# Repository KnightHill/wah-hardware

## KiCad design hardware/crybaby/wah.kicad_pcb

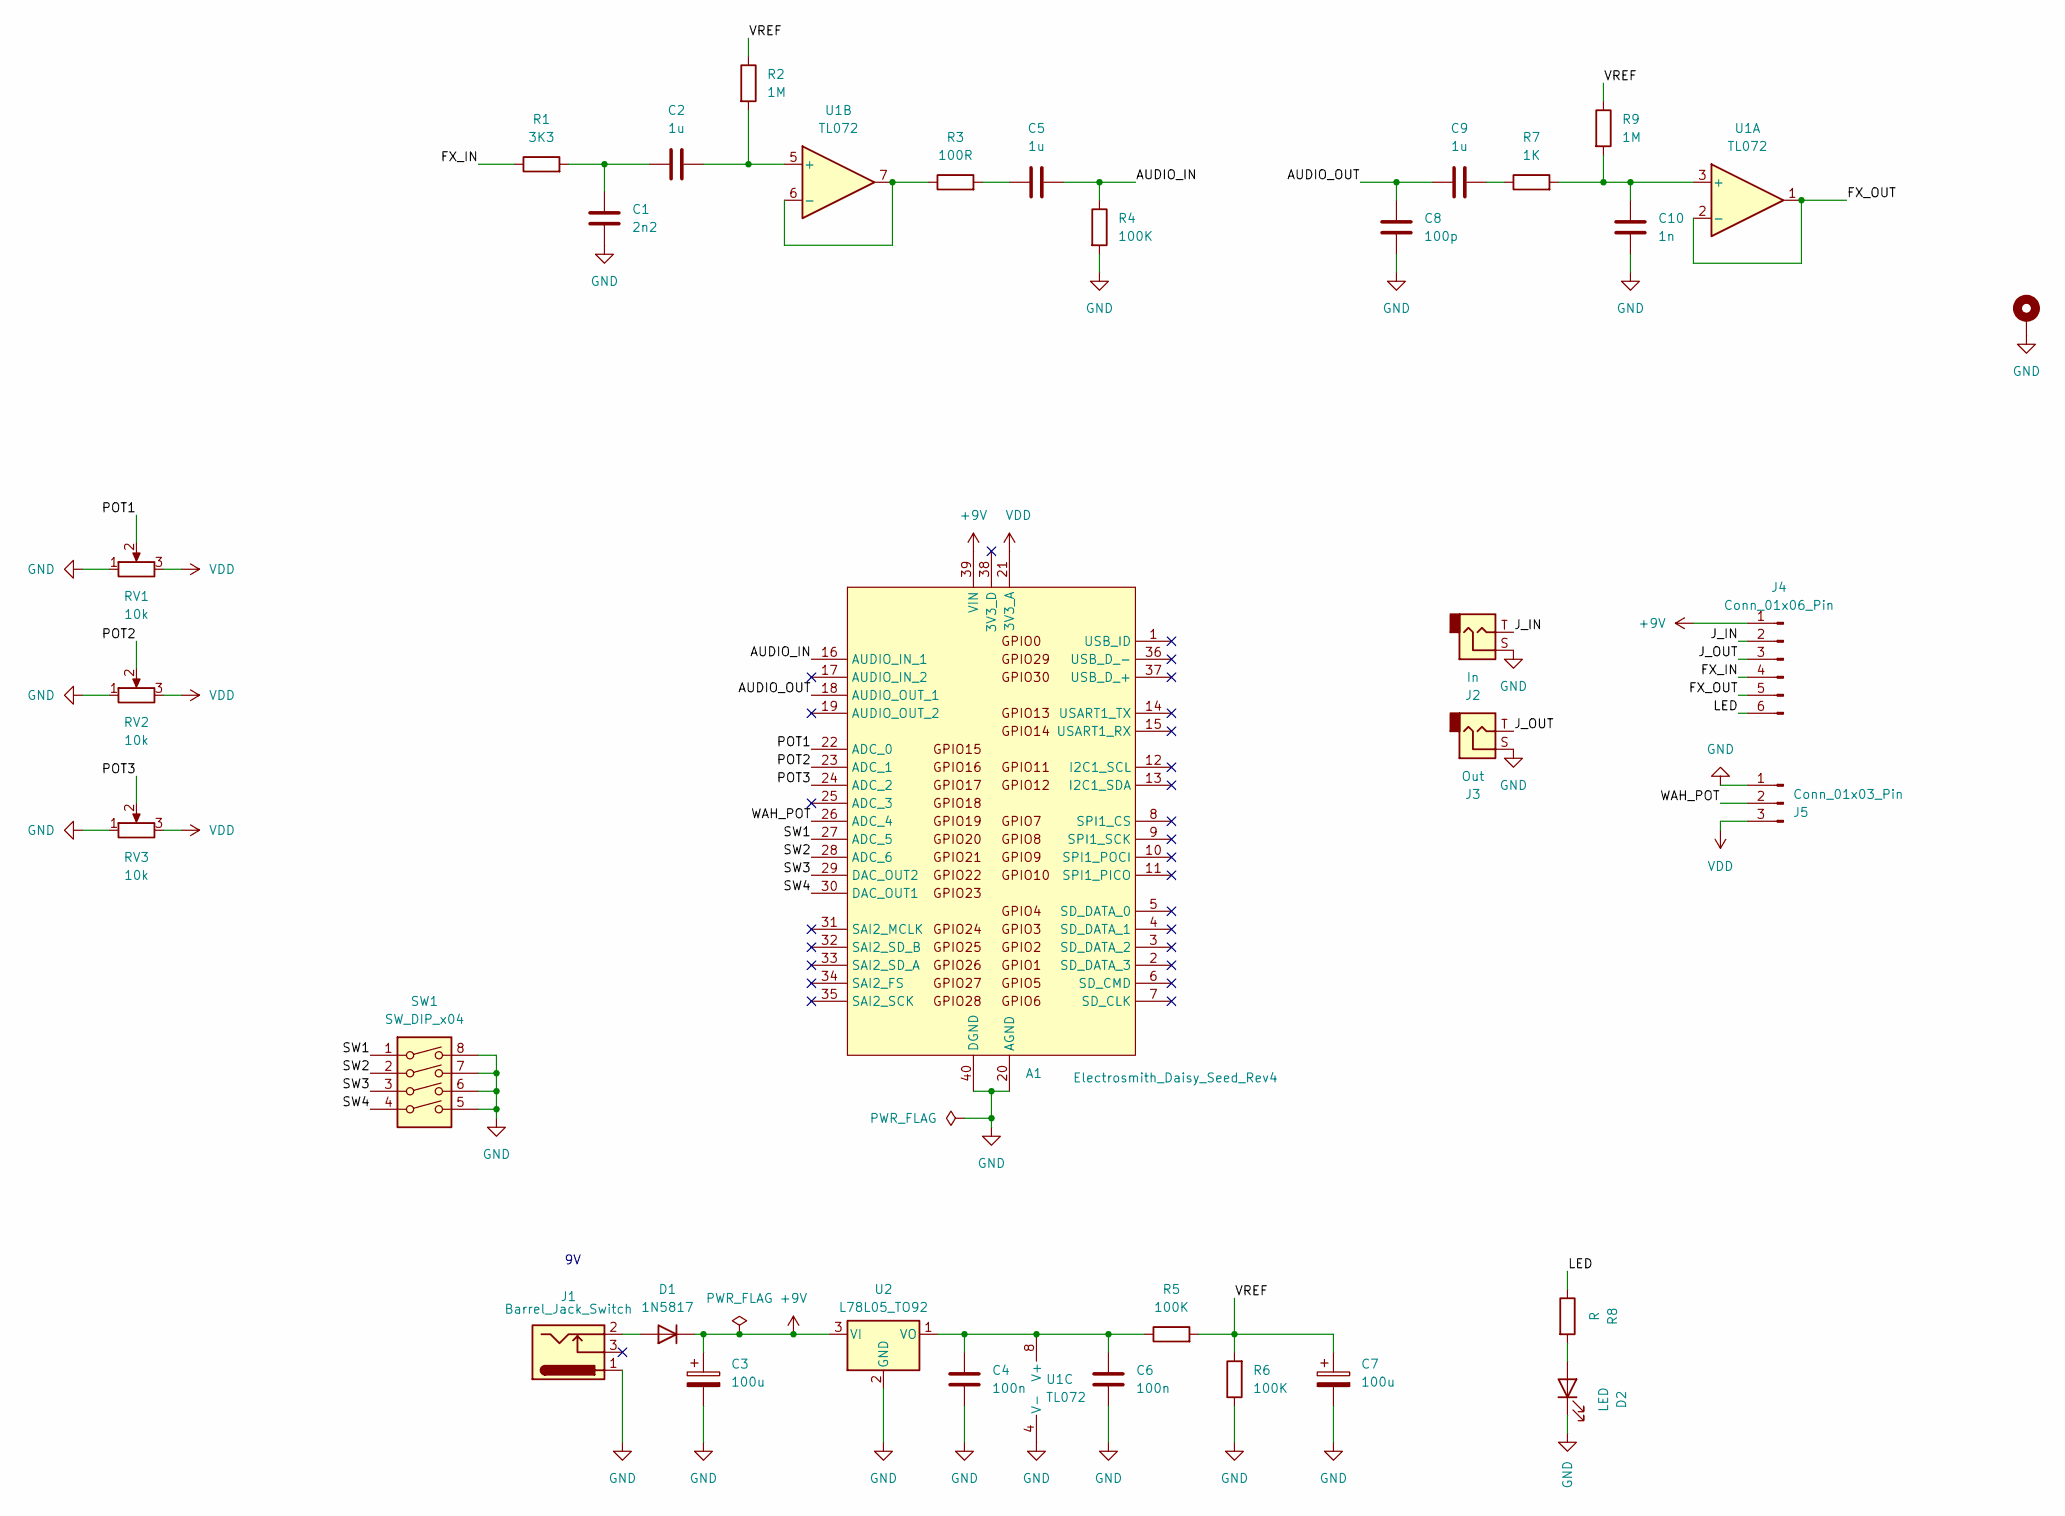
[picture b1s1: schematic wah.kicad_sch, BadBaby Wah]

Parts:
A1: Electrosmith_Daisy_Seed_Rev4; Electrosmith_Daisy_Seed
C1: 2n2; C_Rect_L7.0mm_W2.5mm_P5.00mm
C2, C5, C9: 1u; C_Rect_L7.0mm_W4.5mm_P5.00mm
C3, C7: 100u; CP_Radial_D5.0mm_P2.50mm
C4, C6: 100n; C_Rect_L7.0mm_W2.5mm_P5.00mm
C8: 100p; C_Rect_L7.0mm_W2.5mm_P5.00mm
C10: 1n; C_Rect_L7.0mm_W4.5mm_P5.00mm
D1: 1N5817; D_A-405_P7.62mm_Horizontal
D2: LED; LED_D5.0mm
H1: MountingHole_Pad; MountingHole_4.5mm_Pad
J1: Barrel_Jack_Switch; Generic_PowerJack
J2: In; Jack_6.35mm_Neutrik_NMJ4HCD2_Horizontal
J3: Out; Jack_6.35mm_Neutrik_NMJ4HCD2_Horizontal
J4: Conn_01x06_Pin; PinHeader_1x06_P2.54mm_Vertical
J5: Conn_01x03_Pin; PinHeader_1x03_P2.54mm_Vertical
R1: 3K3; R_Axial_DIN0207_L6.3mm_D2.5mm_P7.62mm_Horizontal
R2, R9: 1M; R_Axial_DIN0207_L6.3mm_D2.5mm_P7.62mm_Horizontal
R3: 100R; R_Axial_DIN0207_L6.3mm_D2.5mm_P7.62mm_Horizontal
R4, R5, R6: 100K; R_Axial_DIN0207_L6.3mm_D2.5mm_P7.62mm_Horizontal
R7: 1K; R_Axial_DIN0207_L6.3mm_D2.5mm_P7.62mm_Horizontal
R8: R; R_Axial_DIN0207_L6.3mm_D2.5mm_P7.62mm_Horizontal
RV1, RV2, RV3: 10k; 3362P
SW1: SW_DIP_x04; SW_DIP_SPSTx04_Slide_9.78x12.34mm_W7.62mm_P2.54mm
U1: TL072; DIP-8_W7.62mm
U2: L78L05_TO92; TO-92_Inline_Wide

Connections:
+9V: A1.39 (VIN), C3.1, D1.1 (K), J4.1, U2.3 (VI)
/AUDIO_IN: A1.16 (AUDIO_IN_1), C5.2, R4.1
/AUDIO_OUT: A1.18 (AUDIO_OUT_1), C8.1, C9.1
/FX_IN: J4.4, R1.1
/FX_OUT: J4.5, U1.1, U1.2 (-)
/J_IN: J2.T, J4.2
/J_OUT: J3.T, J4.3
/LED: J4.6, R8.1
/POT1: A1.22 (ADC_0), RV1.2
/POT2: A1.23 (ADC_1), RV2.2
/POT3: A1.24 (ADC_2), RV3.2
/SW1: A1.27 (ADC_5), SW1.1
/SW2: A1.28 (ADC_6), SW1.2
/SW3: A1.29 (DAC_OUT2), SW1.3
/SW4: A1.30 (DAC_OUT1), SW1.4
/VREF: C7.1, R2.1, R5.2, R6.2, R9.1
/WAH_POT: A1.26 (ADC_4), J5.2
GND: A1.20 (AGND), A1.40 (DGND), C1.2, C3.2, C4.2, C6.2, C7.2, C8.2, C10.2, D2.1 (K), H1.1, J1.1, J2.S, J3.S, J5.1, R4.2, R6.1, RV1.1, RV2.1, RV3.1, SW1.5, SW1.6, SW1.7, SW1.8, U1.4 (V-), U2.2 (GND)
unnamed: C1.1, C2.1, R1.2
unnamed: C5.1, R3.2
unnamed: C9.2, R7.1
unnamed: D1.2 (A), J1.2
unnamed: D2.2 (A), R8.2
unnamed: C10.1, R7.2, R9.2, U1.3 (+)
unnamed: C2.2, R2.2, U1.5 (+)
unnamed: R3.1, U1.6 (-), U1.7
unnamed: C4.1, C6.1, R5.1, U1.8 (V+), U2.1 (VO)
VDD: A1.21 (3V3_A), J5.3, RV1.3, RV2.3, RV3.3

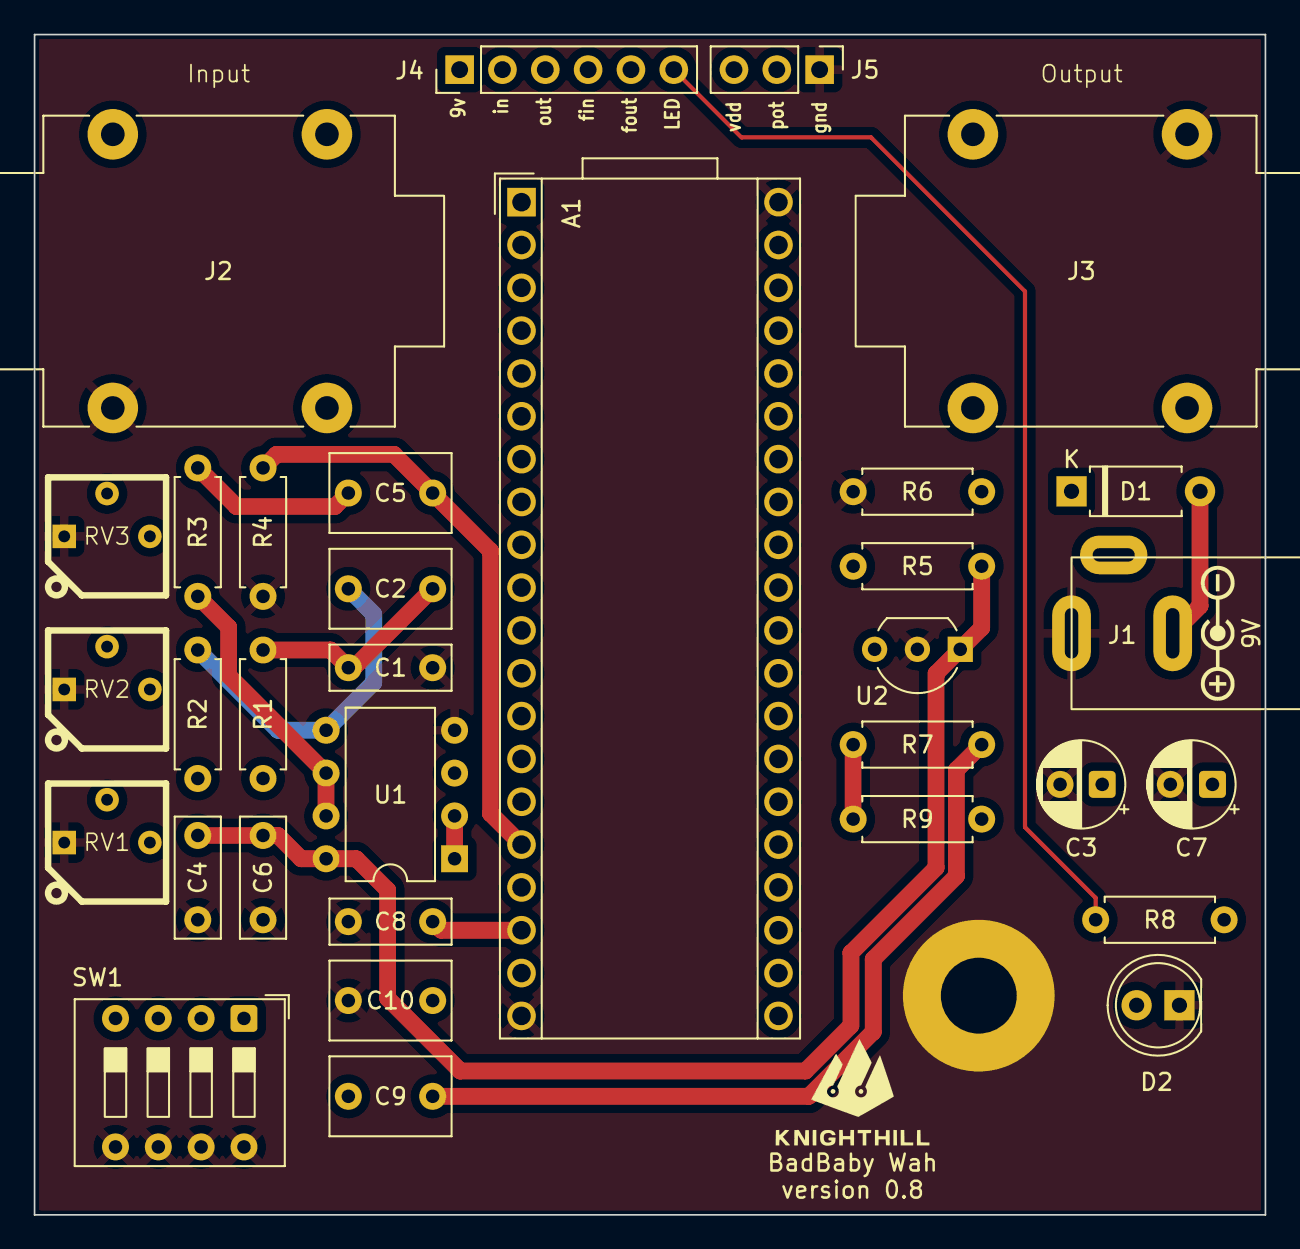
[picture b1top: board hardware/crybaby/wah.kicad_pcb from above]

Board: 4 copper layers, 73.0 x 70.0 mm, 34 parts (0 on the bottom side), 28 nets.

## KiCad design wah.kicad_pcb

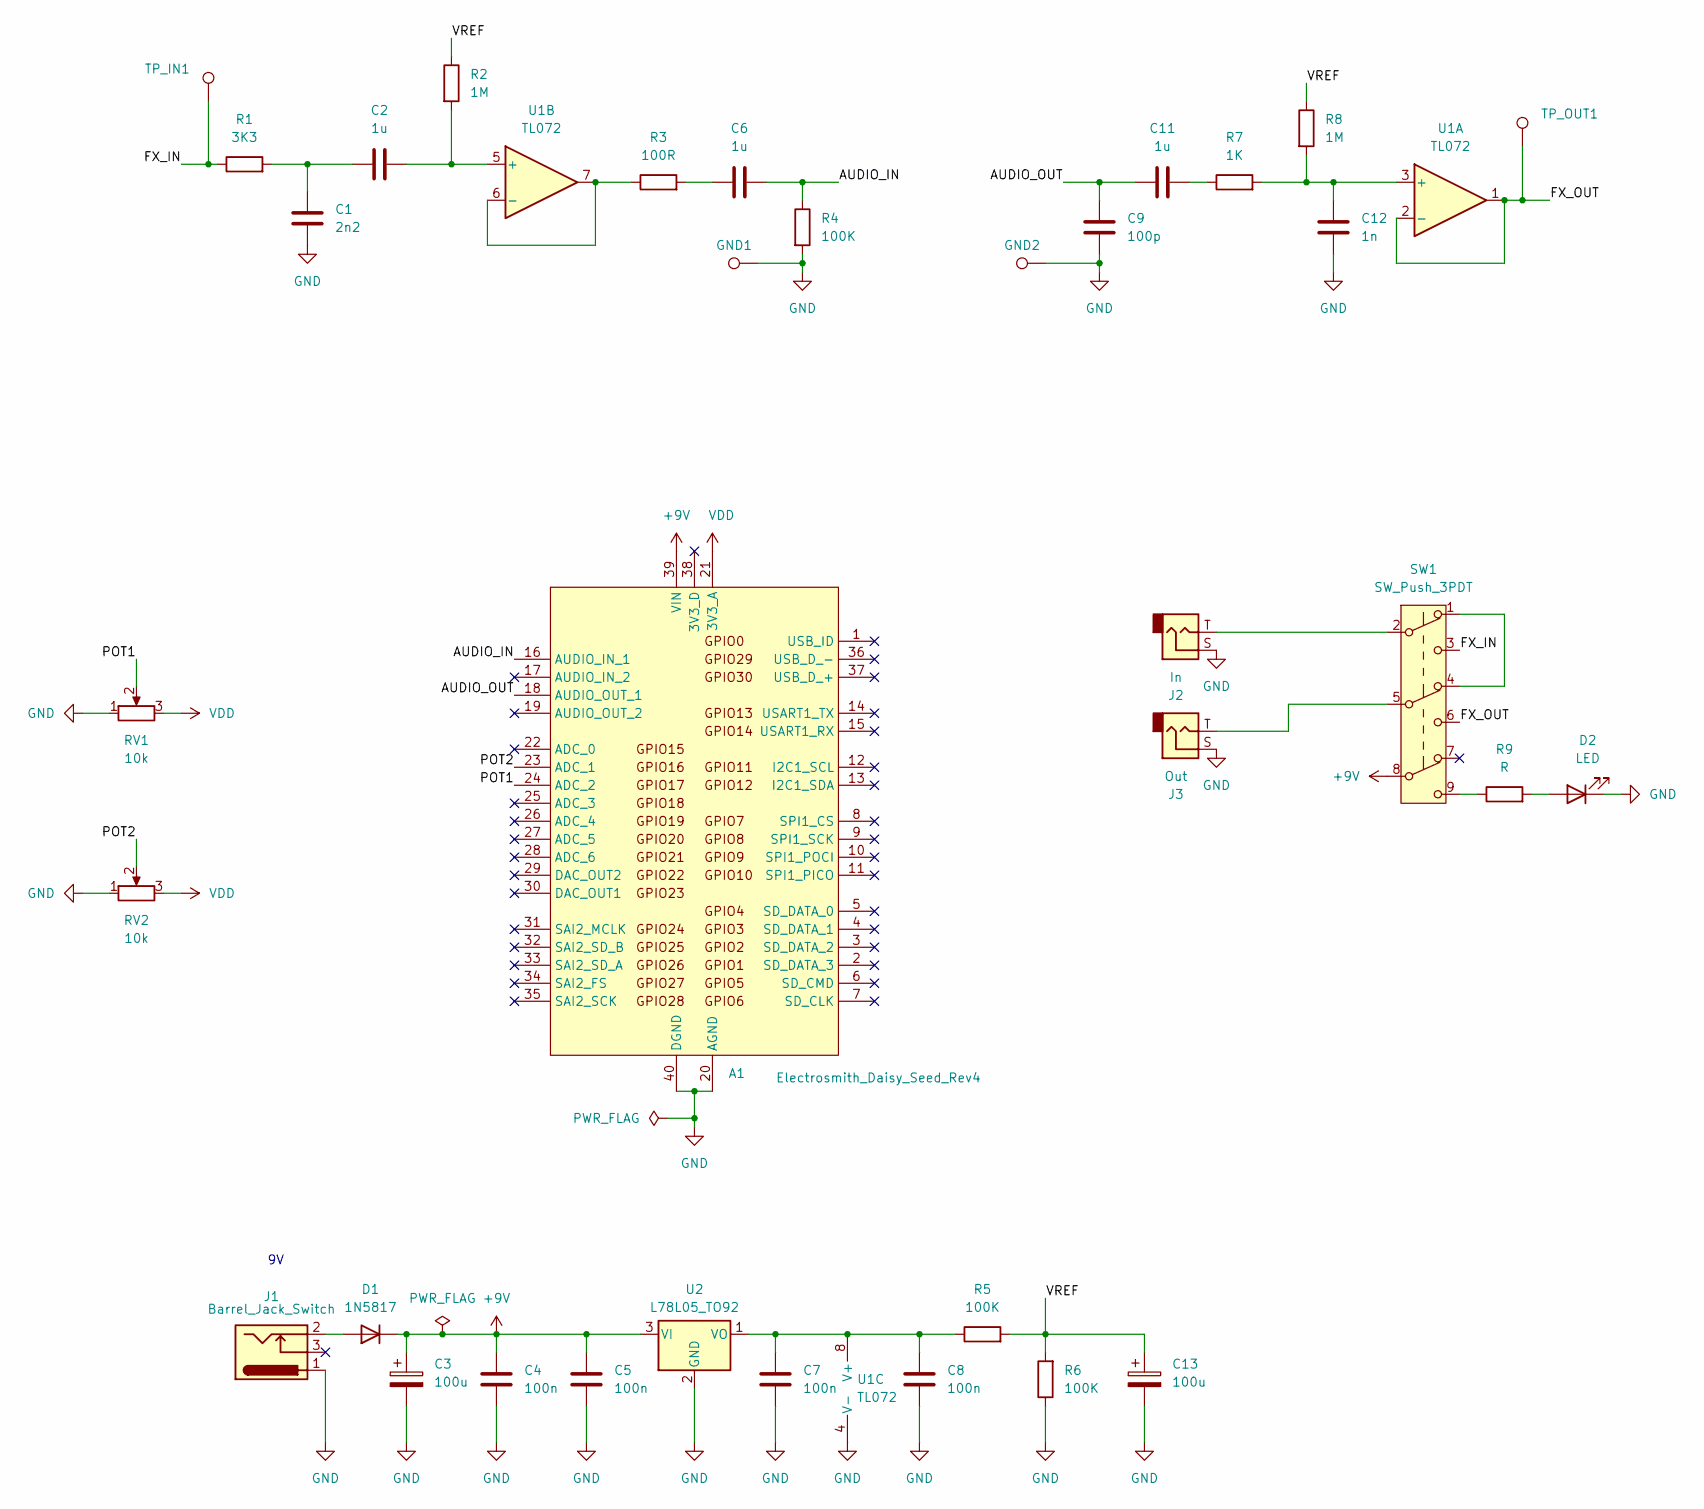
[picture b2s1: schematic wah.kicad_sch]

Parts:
A1: Electrosmith_Daisy_Seed_Rev4; Electrosmith_Daisy_Seed
C1: 2n2; C_Rect_L7.0mm_W2.5mm_P5.00mm
C2, C6, C11: 1u; C_Rect_L7.0mm_W2.5mm_P5.00mm
C3, C13: 100u; CP_Radial_D6.3mm_P2.50mm
C4, C5, C7, C8: 100n; C_Rect_L7.0mm_W2.5mm_P5.00mm
C9: 100p; C_Rect_L7.0mm_W2.5mm_P5.00mm
C12: 1n; C_Rect_L7.0mm_W2.5mm_P5.00mm
D1: 1N5817; D_A-405_P7.62mm_Horizontal
D2: LED; LED_D5.0mm
GND1, GND2: TestPoint_THTPad_1.5x1.5mm_Drill0.7mm
J1: Barrel_Jack_Switch; Generic_PowerJack
J2: In; Jack_6.35mm_Neutrik_NMJ4HCD2_Horizontal
J3: Out; Jack_6.35mm_Neutrik_NMJ4HCD2_Horizontal
R1: 3K3; R_Axial_DIN0207_L6.3mm_D2.5mm_P7.62mm_Horizontal
R2, R8: 1M; R_Axial_DIN0207_L6.3mm_D2.5mm_P7.62mm_Horizontal
R3: 100R; R_Axial_DIN0207_L6.3mm_D2.5mm_P7.62mm_Horizontal
R4, R5, R6: 100K; R_Axial_DIN0207_L6.3mm_D2.5mm_P7.62mm_Horizontal
R7: 1K; R_Axial_DIN0207_L6.3mm_D2.5mm_P7.62mm_Horizontal
R9: R; R_Axial_DIN0207_L6.3mm_D2.5mm_P7.62mm_Horizontal
RV1, RV2: 10k; Potentiometer_uxcel_9mm_Single_Vertical
SW1: SW_Push_3PDT; Switches_Stomp_Switch_3PDT
TP_IN1: TestPoint; TestPoint_THTPad_1.5x1.5mm_Drill0.7mm
TP_OUT1: TestPoint; TestPoint_THTPad_1.5x1.5mm_Drill0.7mm
U1: TL072; DIP-8_W7.62mm
U2: L78L05_TO92; TO-92_Inline_Wide

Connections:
+9V: A1.39 (VIN), C3.1, C4.1, C5.1, D1.1 (K), SW1.8 (B), U2.3 (VI)
/AUDIO_IN: A1.16 (AUDIO_IN_1), C6.2, R4.1
/AUDIO_OUT: A1.18 (AUDIO_OUT_1), C9.1, C11.1
/FX_IN: R1.1, SW1.3 (C), TP_IN1.1
/FX_OUT: SW1.6 (C), TP_OUT1.1, U1.1, U1.2 (-)
/POT1: A1.24 (ADC_2), RV1.2
/POT2: A1.23 (ADC_1), RV2.2
/VREF: C13.1, R2.1, R5.2, R6.2, R8.1
GND: A1.20 (AGND), A1.40 (DGND), C1.2, C3.2, C4.2, C5.2, C7.2, C8.2, C9.2, C12.2, C13.2, D2.1 (K), GND1.1, GND2.1, J1.1, J2.S, J3.S, R4.2, R6.1, RV1.1, RV2.1, U1.4 (V-), U2.2 (GND)
unnamed: C1.1, C2.1, R1.2
unnamed: C6.1, R3.2
unnamed: C11.2, R7.1
unnamed: D1.2 (A), J1.2
unnamed: D2.2 (A), R9.2
unnamed: J2.T, SW1.2 (B)
unnamed: J3.T, SW1.5 (B)
unnamed: R9.1, SW1.9 (C)
unnamed: SW1.1 (A), SW1.4 (A)
unnamed: C12.1, R7.2, R8.2, U1.3 (+)
unnamed: C2.2, R2.2, U1.5 (+)
unnamed: R3.1, U1.6 (-), U1.7
unnamed: C7.1, C8.1, R5.1, U1.8 (V+), U2.1 (VO)
VDD: A1.21 (3V3_A), RV1.3, RV2.3

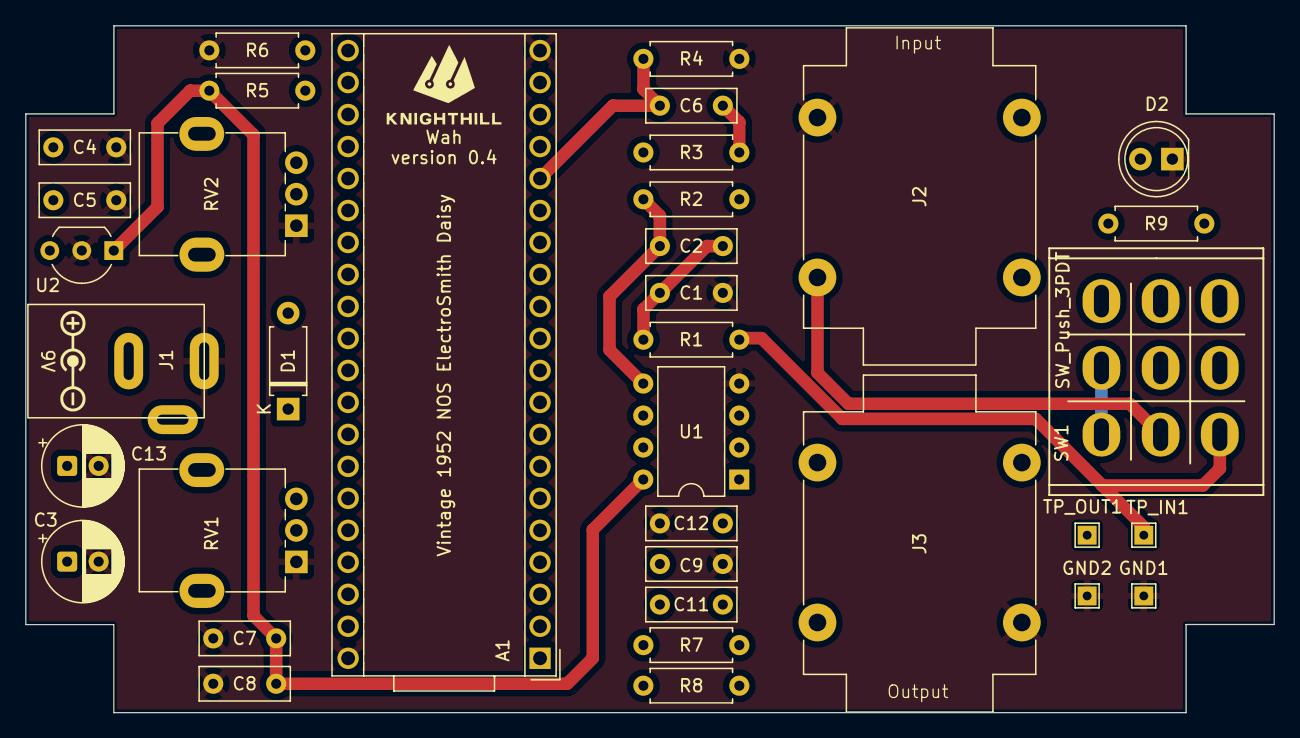
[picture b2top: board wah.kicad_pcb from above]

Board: 4 copper layers, 99.1 x 54.5 mm, 36 parts (0 on the bottom side), 23 nets.

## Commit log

2025-10-30 improve pcb
2025-10-31 add fab files
2025-10-31 fix errors
2025-11-02 reaarange power
2025-11-02 add enclosure corners
2025-11-10 remove probes
2025-11-10 polish pcb
2025-11-11 optimize pcb
2025-11-11 move LED resistor
2025-11-13 create new folders
2025-11-13 add test app
2025-11-13 add volume ctrl
2025-11-14 fix 2 ADC channels
2025-11-14 add wah filters
2025-11-14 optimize pot values
2025-11-14 adding the platform folder
2025-11-14 bug fix
2025-11-14 fix footprints
2025-11-14 rearrange pcb
2025-11-14 rename resources
2025-11-15 move opamp under daisy
2025-11-15 improve layout
2025-11-15 pcb changes
2025-11-16 major rearrangement
2025-11-16 add wah man gerber files
2025-11-16 fix mirror
2025-11-16 separate wah C++ projects
2025-11-16 decrease max Q. add LED blink on boot
2025-11-17 factor
2025-11-17 todo note
2025-11-18 add taper function
2025-11-18 add taper functions
2025-11-18 add dead zome taper
2025-11-19 extend taper selection
2025-11-19 remove range function
2025-11-19 readme
2025-11-21 Add full taper
2025-11-21 improve taper class
2025-11-21 refactor
2025-11-22 add CB dimention
2025-11-23 finalze pcb
2025-11-23 remove pot 4
2025-11-23 add trimmer footprint
2025-11-23 improve trimmer footprint
2025-11-24 new fab files
2025-11-28 add gitignore
2025-11-30 streamline two filter wah
2025-11-30 fix fmap calls
2025-11-30 add vowel formants
2025-12-01 add taper to 2filter wah
2025-12-02 add debug
